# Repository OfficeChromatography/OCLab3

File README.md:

# OC-Control 
A Marlin 2.0 3D Printer based Firmware

## Marlin 2.0

Marlin 2.0 takes this popular RepRap firmware to the next level by adding support for much faster 32-bit and ARM-based boards while improving support for 8-bit AVR boards. Read about Marlin's decision to use a "Hardware Abstraction Layer" below.

Download earlier versions of Marlin on the [Releases page](https://github.com/MarlinFirmware/Marlin/releases).

## Building OC-Control

To build OC-Control [PlatformIO](http://docs.platformio.org/en/latest/ide.html#platformio-ide) is preferred. Detailed build and install instructions are posted at:

  - [Installing Marlin (VSCode)](http://marlinfw.org/docs/basics/install_platformio_vscode.html).

If you need more help, follow our [instruction_visualstudio-code](https://github.com/OfficeChromatography/OCLab3/blob/master/instruction_visualstudio-code), available above in the OCLab3 folder.

# OC-Manager 3 SOFTWARE
OC-Manager 3 installation 
[OC-Manager3](https://github.com/OfficeChromatography/OCLab3-Software)

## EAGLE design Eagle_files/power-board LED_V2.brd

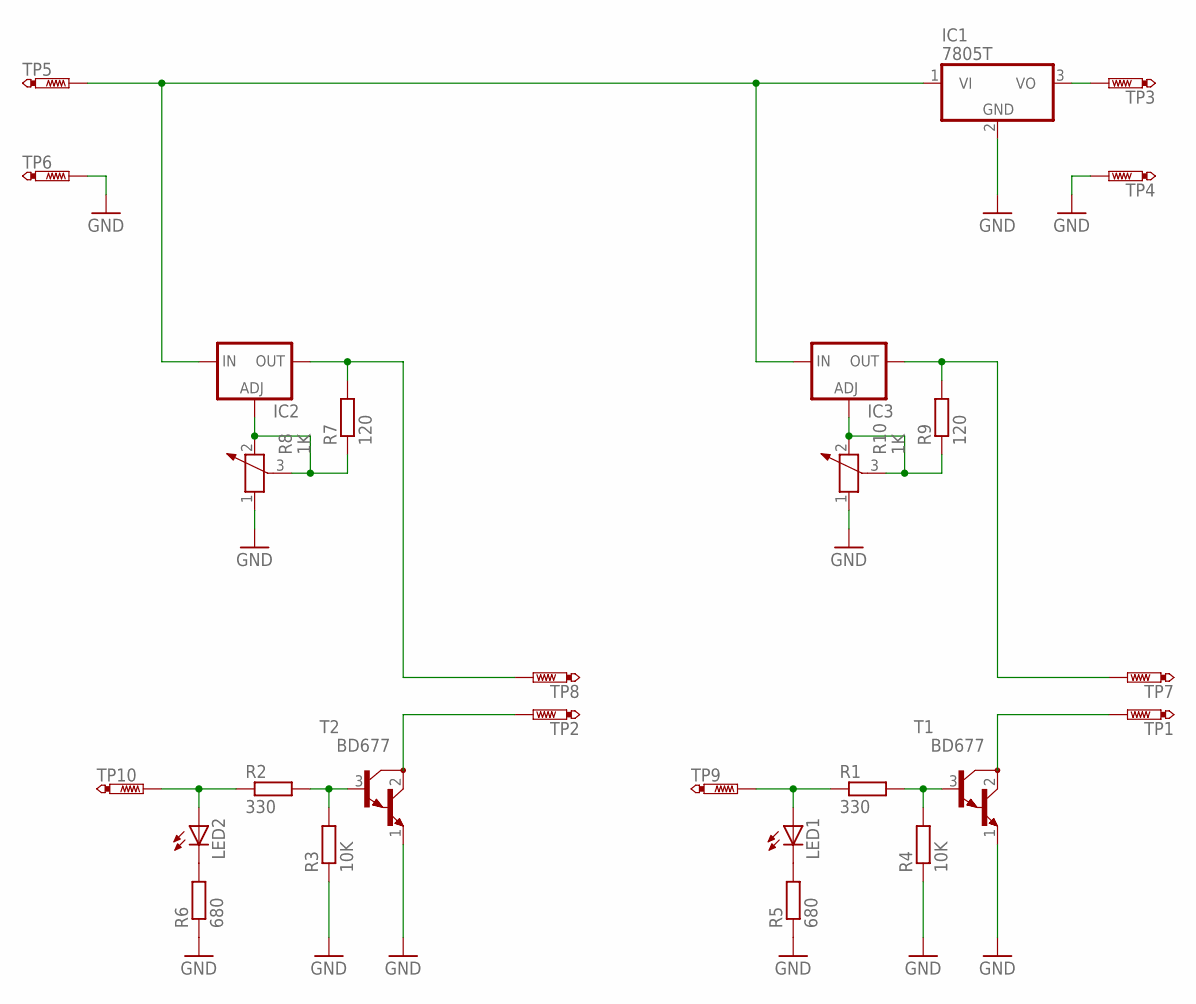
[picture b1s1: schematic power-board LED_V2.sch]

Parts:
IC1: 7805T; TO220H
IC2, IC3: LM317TS; 317TS
LED1, LED2: LED3MM
R1, R2: 330; 0207/10
R3, R4: 10K; 0207/10
R5, R6: 680; 0207/10
R7, R9: 120; 0207/10
R8, R10: 1K; PT-10
T1, T2: BD677; TO126
TP1, TP2, TP3, TP4, TP5, TP6, TP7, TP8, TP9, TP10: PTR1PAD1-17; P1-17

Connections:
GND: IC1.2 (GND), R3.1, R4.1, R5.1, R6.1, R8.1, R10.1, T1.1 (E), T2.1 (E), TP4.TP, TP6.TP
unnamed: R1.2, R4.2, T1.3 (B)
unnamed: LED1.A, R1.1, TP9.TP
unnamed: T1.2 (C), TP1.TP
unnamed: R2.2, R3.2, T2.3 (B)
unnamed: LED2.A, R2.1, TP10.TP
unnamed: T2.2 (C), TP2.TP
unnamed: IC1.3 (VO), TP3.TP
unnamed: LED1.K (C), R5.2
unnamed: LED2.K (C), R6.2
unnamed: IC2.1 (ADJ), R7.1, R8.2, R8.3
unnamed: IC3.1 (ADJ), R9.1, R10.2, R10.3
unnamed: IC3.2 (OUT), R9.2, TP7.TP
unnamed: IC2.2 (OUT), R7.2, TP8.TP
unnamed: IC1.1 (VI), IC2.3 (IN), IC3.3 (IN), TP5.TP

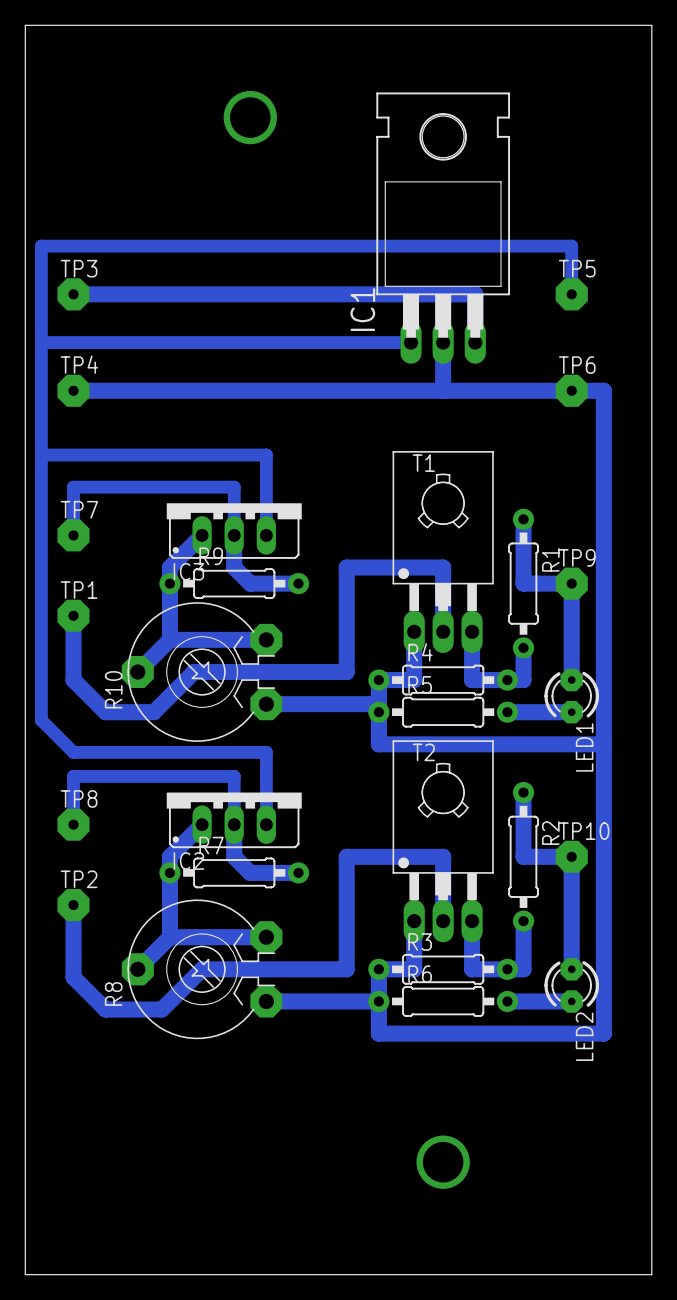
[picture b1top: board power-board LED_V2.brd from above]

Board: 2 copper layers, 49.5 x 98.7 mm, 27 parts (0 on the bottom side), 15 nets.

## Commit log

2020-04-23 Pump Working
2020-04-23 Correct config
2020-04-27 Pump Working with preassure checks
2020-05-12 Mostly working
2020-08-18 Last Version with cleaning
2020-09-10 Working with crapy sensor
2020-09-25 last version
2020-09-30 NeoPixelLEDS
2020-09-30 g40 working
2020-10-01 new valve class
2020-10-08 openValve and cV will trigger the pin
2020-10-08 changed maxOpenPeriod to 10s
2020-10-22 set maxOpentime to 30s
2020-11-10 added checkEndstop for E Stepper Motor
2020-11-11 adding E0 driver
2020-11-17 Fix pressure sensor
2020-11-23 added g41 code
2020-11-23 cleaned up the code
2020-11-27 New G95 OPTIONS
2020-11-27 New PID constants
2020-12-01 deleted extrudeEndstop
2020-12-02 fan update
2020-12-02 rebase with nozzledown
2020-12-02 getZero enabled on startup
2021-01-08 LastWorking version
2021-01-08 enabled Force sensor
2021-05-18 Latest version
2021-06-30 TM2130, OPTICAL ENDSTOP, NEW PUMPCONTROL
2021-09-14 New Motor
2021-09-15 New Motor config
2021-09-22 last changes
2021-09-22 improve syringe load
2021-09-22 More accerleration
2021-10-12 add dht humidity sensor
2021-10-12 fix import dht
2021-10-12 Add STL Files
2021-10-12 Add software in md
2021-10-20 Added Freecad File
    Move STLs to 3DParts folder and added FreeCad
2021-10-25 NEW firmware
2021-10-25 force sensor begin disable
2021-10-29 New Syringe pusher.stl Fix bug with ElectronicBox
2021-10-29 New Camera holder, 5mm to the right
2021-11-01 axis per step
2021-11-18 new bigger development cart
2021-11-18 new pump
2021-12-01 new pressure sensor initial and temp max
2021-12-20 remove syringe load verification
2021-12-22 Comments for pitch added
2021-12-25 Instruction VSCode added
2022-03-10 corrections
2022-03-10 files added
2022-03-21 Marlin corrected
2022-03-31 corrected
2022-04-12 removed download TMC26XX git repo
2022-04-14 Create include
2022-04-14 include folder added
2022-04-19 eagle files added
2022-04-22 modification
2022-07-13 stl added
2022-07-27 Z_MAX_POS changed to 60
2024-08-13 upload
